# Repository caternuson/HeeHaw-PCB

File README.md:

# HeeHaw-PCB
Developmental seesaw board

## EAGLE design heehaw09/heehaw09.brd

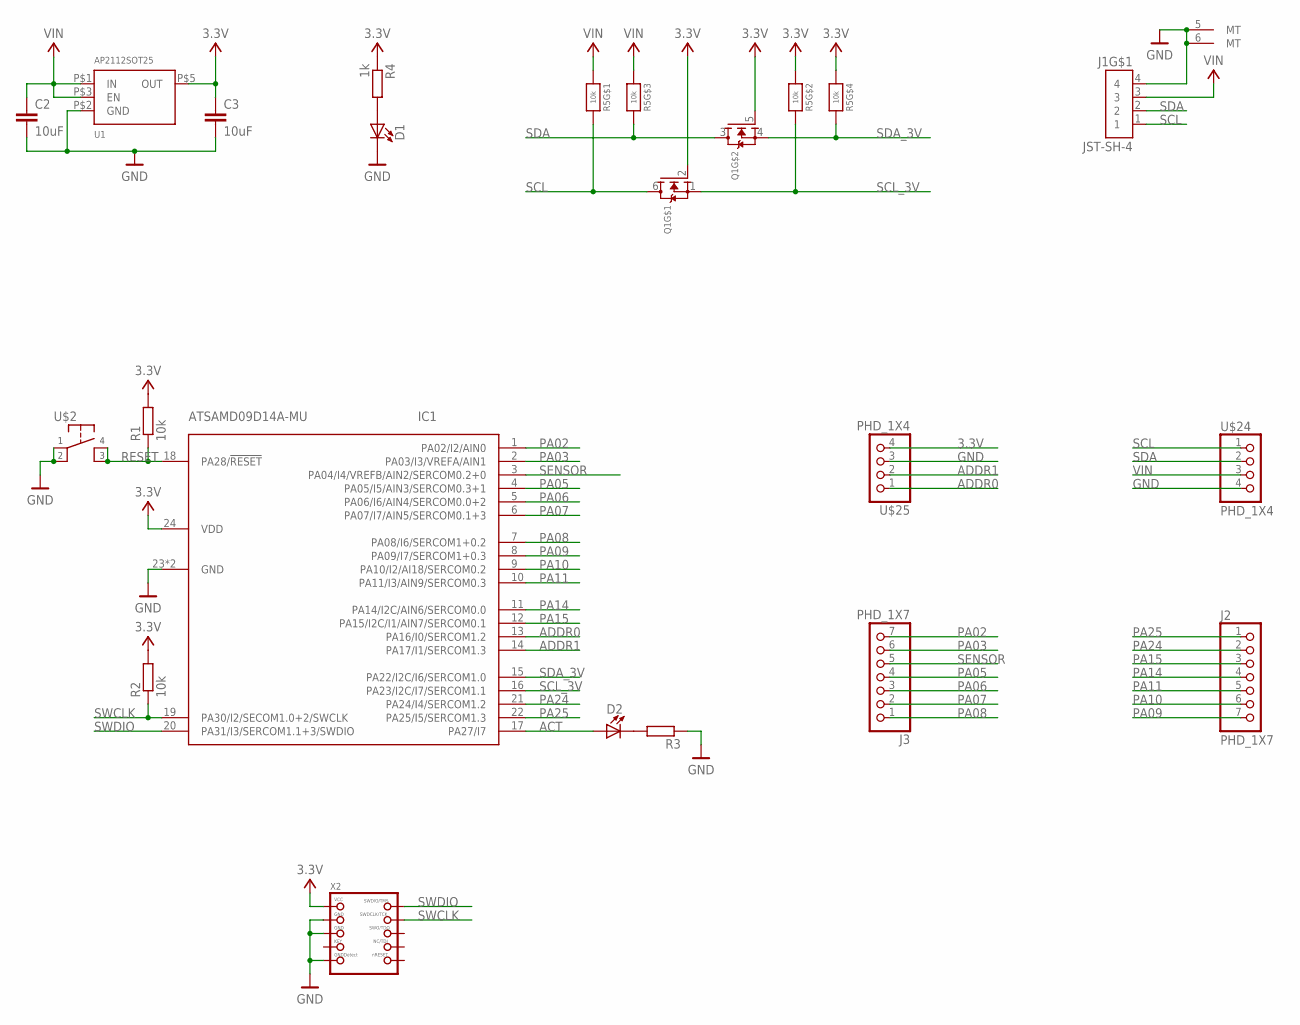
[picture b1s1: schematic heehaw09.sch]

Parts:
C2, C3: 10uF; C0603
D1, D2: SMD_LED0603; LED0603
IC1: ATSAMD09D14A-MU; QFN24_4MM
J1: JST-SH-4; JST-S4B-SH-SM4-TB
J2, J3: PHD_1X7
Q1: MOSFET-N_DUAL; SOT363
R1, R2: 10k; R0603
R3: R-EU_R0603; R0603
R4: 1k; R0603
R5: 10k; RESPACK_4X0603
U1: AP2112SOT25; SOT25
U$2: PTS647
U$24, U$25: PHD_1X4
X2: SWD_2X5; SWD_MINI

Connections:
3.3V: C3.1, IC1.24 (VDD), Q1.2 (G), Q1.5 (G), R1.2, R2.2, R4.1, R5.2 (1), R5.4 (1), U1.P$5 (OUT), U$25.4, X2.1 (VCC)
ACT: D2.2 (A), IC1.17 (PA27/I7)
ADDR0: IC1.13 (PA16/I0/SERCOM1.2), U$25.1
ADDR1: IC1.14 (PA17/I1/SERCOM1.3), U$25.2
GND: C2.2, C3.2, D1.1 (C), IC1.23 (GND), IC1.THERM (GND), J1.4, J1.5 (MT), J1.6 (MT), R3.1, U1.P$2 (GND), U$2.1, U$2.2, U$24.4, U$25.3, X2.3 (GND), X2.5 (GND), X2.9 (GNDDETECT)
unnamed: D1.2 (A), R4.2
unnamed: D2.1 (C), R3.2
PA02: IC1.1 (PA02/I2/AIN0), J3.7
PA03: IC1.2 (PA03/I3/VREFA/AIN1), J3.6
PA05: IC1.4 (PA05/I5/AIN3/SERCOM0.3+1), J3.4
PA06: IC1.5 (PA06/I6/AIN4/SERCOM0.0+2), J3.3
PA07: IC1.6 (PA07/I7/AIN5/SERCOM0.1+3), J3.2
PA08: IC1.7 (PA08/I6/SERCOM1+0.2), J3.1
PA09: IC1.8 (PA09/I7/SERCOM1+0.3), J2.7
PA10: IC1.9 (PA10/I2/AI18/SERCOM0.2), J2.6
PA11: IC1.10 (PA11/I3/AIN9/SERCOM0.3), J2.5
PA14: IC1.11 (PA14/I2C/AIN6/SERCOM0.0), J2.4
PA15: IC1.12 (PA15/I2C/I1/AIN7/SERCOM0.1), J2.3
PA24: IC1.21 (PA24/I4/SERCOM1.2), J2.2
PA25: IC1.22 (PA25/I5/SERCOM1.3), J2.1
RESET: IC1.18 (PA28/!RESET), R1.1, U$2.3, U$2.4
SCL: J1.1, Q1.6 (D), R5.8 (2), U$24.1
SCL_3V: IC1.16 (PA23/I2C/I7/SERCOM1.1), Q1.1 (S), R5.7 (2)
SDA: J1.2, Q1.3 (D), R5.6 (2), U$24.2
SDA_3V: IC1.15 (PA22/I2C/I6/SERCOM1.0), Q1.4 (S), R5.5 (2)
SENSOR: IC1.3 (PA04/I4/VREFB/AIN2/SERCOM0.2+0), J3.5
SWCLK: IC1.19 (PA30/I2/SECOM1.0+2/SWCLK), R2.1, X2.4 (SWDCLK)
SWDIO: IC1.20 (PA31/I3/SERCOM1.1+3/SWDIO), X2.2 (SWDIO)
VIN: C2.1, J1.3, R5.1, R5.3 (1), U1.P$1 (IN), U1.P$3 (EN), U$24.3

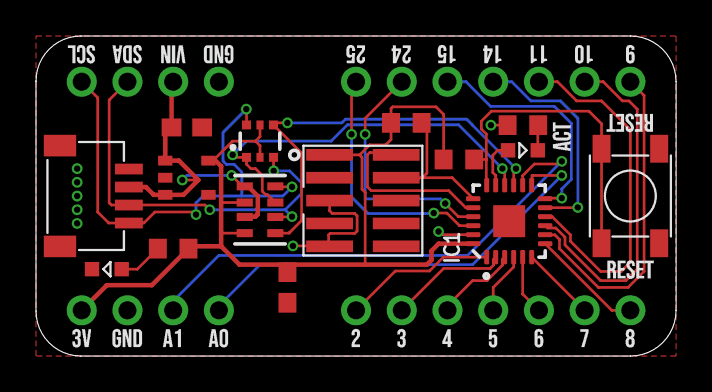
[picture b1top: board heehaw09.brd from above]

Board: 2 copper layers, 35.6 x 17.8 mm, 19 parts (0 on the bottom side), 29 nets.

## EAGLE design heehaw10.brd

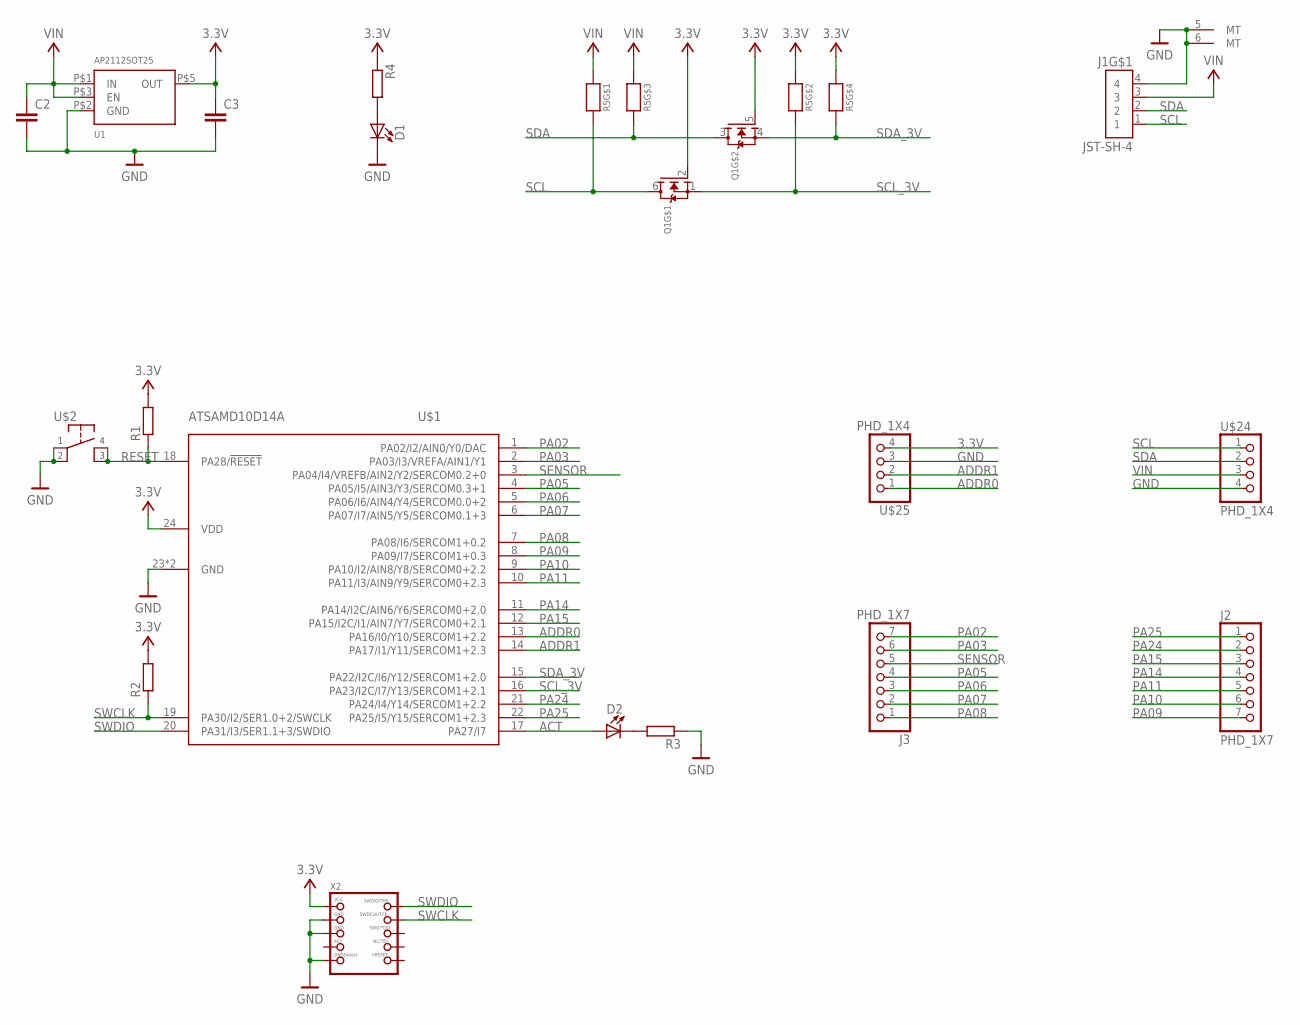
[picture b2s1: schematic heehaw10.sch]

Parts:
C2, C3: C-EUC0603; C0603
D1, D2: SMD_LED0603; LED0603
J1: JST-SH-4; JST-S4B-SH-SM4-TB
J2, J3: PHD_1X7
Q1: MOSFET-N_DUAL; SOT363
R1, R2, R3, R4: R-EU_R0603; R0603
R5: RESISTOR_4PACK; RESPACK_4X0603
U1: AP2112SOT25; SOT25
U$1: ATSAMD10D14A; QFN24_4MM
U$2: PTS647
U$24, U$25: PHD_1X4
X2: SWD_2X5; SWD_MINI

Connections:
3.3V: C3.1, Q1.2 (G), Q1.5 (G), R1.2, R2.2, R4.1, R5.2 (1), R5.4 (1), U1.P$5 (OUT), U$1.24 (VDD), U$25.4, X2.1 (VCC)
ACT: D2.2 (A), U$1.17 (PA27/I7)
ADDR0: U$1.13 (PA16/I0/Y10/SERCOM1+2.2), U$25.1
ADDR1: U$1.14 (PA17/I1/Y11/SERCOM1+2.3), U$25.2
GND: C2.2, C3.2, D1.1 (C), J1.4, J1.5 (MT), J1.6 (MT), R3.1, U1.P$2 (GND), U$1.23 (GND), U$1.THERM (GND), U$2.1, U$2.2, U$24.4, U$25.3, X2.3 (GND), X2.5 (GND), X2.9 (GNDDETECT)
unnamed: D1.2 (A), R4.2
unnamed: D2.1 (C), R3.2
PA02: J3.7, U$1.1 (PA02/I2/AIN0/Y0/DAC)
PA03: J3.6, U$1.2 (PA03/I3/VREFA/AIN1/Y1)
PA05: J3.4, U$1.4 (PA05/I5/AIN3/Y3/SERCOM0.3+1)
PA06: J3.3, U$1.5 (PA06/I6/AIN4/Y4/SERCOM0.0+2)
PA07: J3.2, U$1.6 (PA07/I7/AIN5/Y5/SERCOM0.1+3)
PA08: J3.1, U$1.7 (PA08/I6/SERCOM1+0.2)
PA09: J2.7, U$1.8 (PA09/I7/SERCOM1+0.3)
PA10: J2.6, U$1.9 (PA10/I2/AIN8/Y8/SERCOM0+2.2)
PA11: J2.5, U$1.10 (PA11/I3/AIN9/Y9/SERCOM0+2.3)
PA14: J2.4, U$1.11 (PA14/I2C/AIN6/Y6/SERCOM0+2.0)
PA15: J2.3, U$1.12 (PA15/I2C/I1/AIN7/Y7/SERCOM0+2.1)
PA24: J2.2, U$1.21 (PA24/I4/Y14/SERCOM1+2.2)
PA25: J2.1, U$1.22 (PA25/I5/Y15/SERCOM1+2.3)
RESET: R1.1, U$1.18 (PA28/!RESET), U$2.3, U$2.4
SCL: J1.1, Q1.6 (D), R5.8 (2), U$24.1
SCL_3V: Q1.1 (S), R5.7 (2), U$1.16 (PA23/I2C/I7/Y13/SERCOM1+2.1)
SDA: J1.2, Q1.3 (D), R5.6 (2), U$24.2
SDA_3V: Q1.4 (S), R5.5 (2), U$1.15 (PA22/I2C/I6/Y12/SERCOM1+2.0)
SENSOR: J3.5, U$1.3 (PA04/I4/VREFB/AIN2/Y2/SERCOM0.2+0)
SWCLK: R2.1, U$1.19 (PA30/I2/SER1.0+2/SWCLK), X2.4 (SWDCLK)
SWDIO: U$1.20 (PA31/I3/SER1.1+3/SWDIO), X2.2 (SWDIO)
VIN: C2.1, J1.3, R5.1, R5.3 (1), U1.P$1 (IN), U1.P$3 (EN), U$24.3

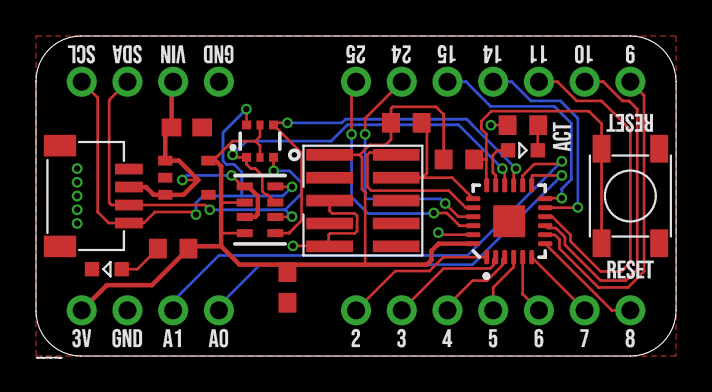
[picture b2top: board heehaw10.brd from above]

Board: 2 copper layers, 35.6 x 17.8 mm, 19 parts (0 on the bottom side), 29 nets.

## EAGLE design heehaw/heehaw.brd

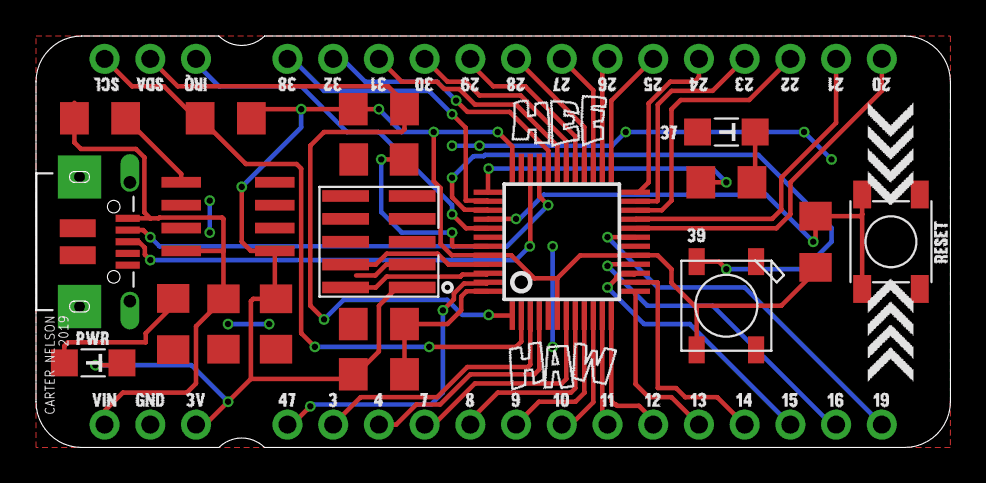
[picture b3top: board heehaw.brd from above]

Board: 2 copper layers, 50.8 x 22.9 mm, 23 parts (0 on the bottom side), 46 nets.

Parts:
C1, C2, C3: 1uF; C1206
D1, D3: LED1206
R1, R2, R4, R5, R6, R7, R8: R1206
R3: 10K; R1206
U2: AP2112-SO08; SO08
U$1: ATSAMD21G; TQFP48_7MM
U$2: PTS647
U$10, U$11: PHD_1X3
U$20: NEOPIXEL_5050; WS2812B_5050
U$24, U$28: PHD_1X14
X1: SWD_MINI
X2: USB_MICRO_B

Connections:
3.3V: C3.1, D3.2, R1.2, R2.2, R5.2, R7.2, U2.1, U$1.6, U$1.17, U$1.36, U$1.44, U$10.3, U$20.1-VDD, X1.1
D+: U$1.34, X2.D+
D-: U$1.33, X2.D-
GND: C1.2, C2.2, C3.2, D1.1, R4.1, R8.1, U2.6, U2.7, U$1.5, U$1.18, U$1.35, U$1.42, U$2.1, U$2.2, U$10.2, U$20.3-GND, X1.3, X1.5, X1.9, X2.BASE@1, X2.BASE@2, X2.GND, X2.SPRT@1, X2.SPRT@2, X2.SPRT@3, X2.SPRT@4
IRQ: U$1.41, U$11.1
unnamed: D3.1, R4.2
unnamed: R3.1, U2.5
unnamed: R5.1, U$1.40, U$2.3, U$2.4
unnamed: R6.2, U$1.37
unnamed: D1.2, R6.1
unnamed: R7.1, R8.2, U$1.48
unnamed: C1.1, U$1.43
NEO: U$1.39, U$20.4-DIN
P3: U$1.3, U$24.2
P4: U$1.4, U$24.3
P7: U$1.7, U$24.4
P8: U$1.8, U$24.5
P9: U$1.9, U$24.6
P10: U$1.10, U$24.7
P11: U$1.11, U$24.8
P12: U$1.12, U$24.9
P13: U$1.13, U$24.10
P14: U$1.14, U$24.11
P15: U$1.15, U$24.12
P16: U$1.16, U$24.13
P19: U$1.19, U$24.14
P20: U$1.20, U$28.1
P21: U$1.21, U$28.2
P22: U$1.22, U$28.3
P23: U$1.23, U$28.4
P24: U$1.24, U$28.5
P25: U$1.25, U$28.6
P26: U$1.26, U$28.7
P27: U$1.27, U$28.8
P28: U$1.28, U$28.9
P29: U$1.29, U$28.10
P30: U$1.30, U$28.11
P31: U$1.31, U$28.12
P32: U$1.32, U$28.13
P38: U$1.38, U$28.14
P47: U$1.47, U$24.1
SCL: R2.1, U$1.2, U$11.3
SDA: R1.1, U$1.1, U$11.2
SWCLK: U$1.45, X1.4
SWDIO: U$1.46, X1.2
VIN: C2.1, R3.2, U2.8, U$10.1, X2.VBUS

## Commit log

2021-02-07 add files
2021-03-07 add heehaw10
2022-02-09 move stuff
2022-02-09 add heehaw09
